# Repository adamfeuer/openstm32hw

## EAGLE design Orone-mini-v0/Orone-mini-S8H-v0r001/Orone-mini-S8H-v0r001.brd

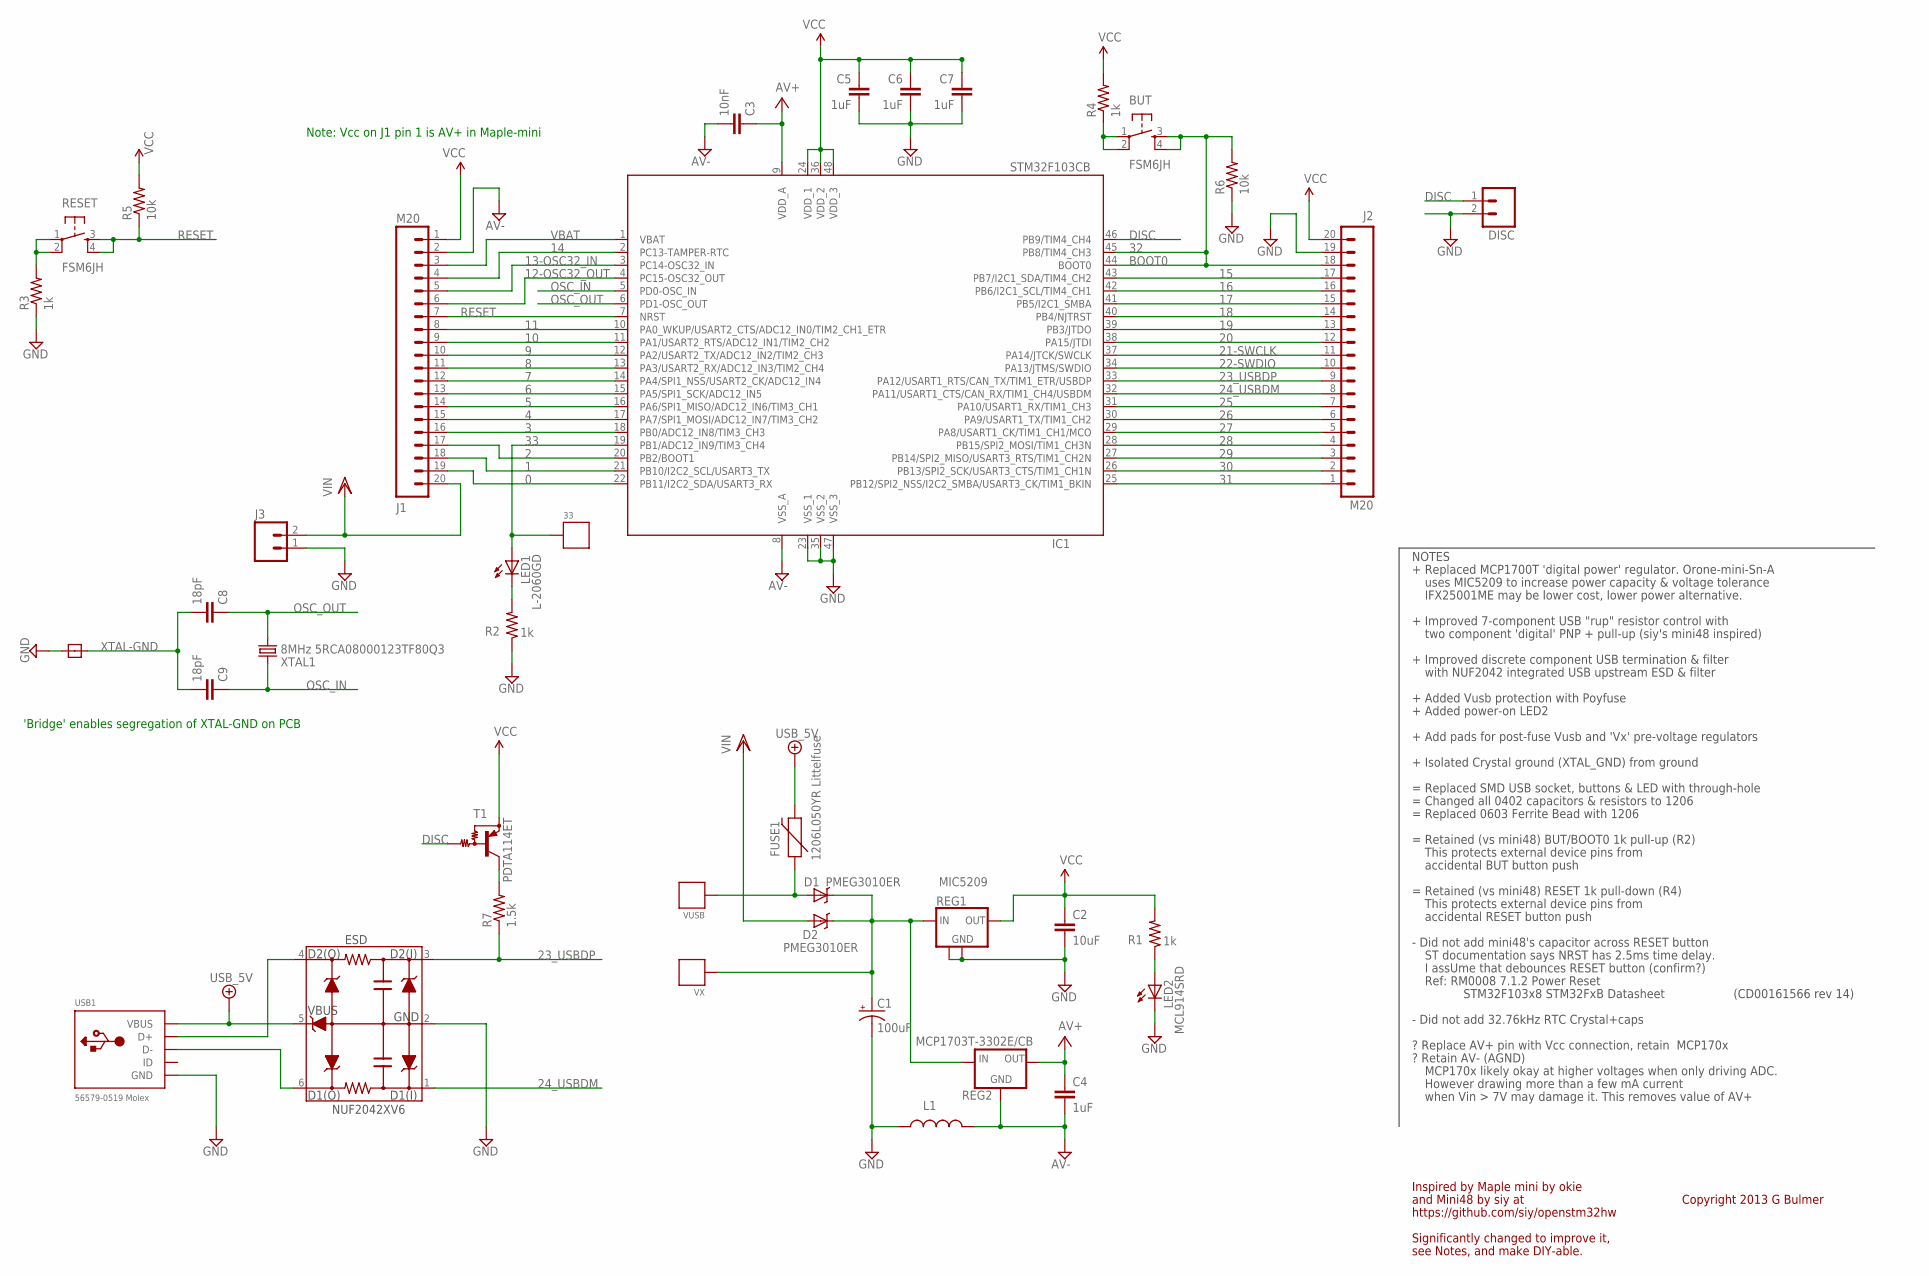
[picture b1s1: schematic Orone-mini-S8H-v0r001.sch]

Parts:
33: SIGNAL-PIN1; 1PIN
BUT: FSM6JH; TACTILE-PTH
C1: 100uF; EIA7343
C2: 10uF; 1206
C3: 10nF; 1206
C4, C5, C6, C7: 1uF; 1206
C8, C9: 18pF; 1206
D1, D2: PMEG3010ER; SOD-123W
DISC: M021X02_NO_SILK; 1X02_NO_SILK
ESD: NUF2042XV6; SOT563
FUSE1: 1206L050YR Littelfuse; PTC-1206
IC1: STM32F103CB; LQFP48
J1, J2: M20; 1X20
J3: M02POLAR; MOLEX-1X2
L1: INDUCTOR1206; 1206
LED1: L-2060GD; LED1.8MM-1MM
LED2: MCL914SRD; LED1.8MM-1MM
R1, R2, R3, R4: 1k; 1206
R5, R6: 10k; 1206
R7: 1.5k; 1206
REG1: MIC5209; SOT223-NT
REG2: MCP1703T-3302E/CB; SOT23
RESET: FSM6JH; TACTILE-PTH
T1: PDTA114ET; ES_SOT23-3
U$4: 2PIN-GND-BRIDGE08X08MILS; 2PIN-08X08
USB1: 56579-0519 Molex; USB-MINI-AB-TH-MOLEX-DRILL
VUSB: SIGNAL-PIN1; 1PIN
VX: SIGNAL-PIN1; 1PIN
XTAL1: 8MHz 5RCA08000123TF80Q3; CRYSTAL-SMD-5X3

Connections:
0: IC1.22 (PB11/I2C2_SDA/USART3_RX), J1.19
1: IC1.21 (PB10/I2C2_SCL/USART3_TX), J1.18
2: IC1.20 (PB2/BOOT1), J1.17
3: IC1.18 (PB0/ADC12_IN8/TIM3_CH3), J1.16
4: IC1.17 (PA7/SPI1_MOSI/ADC12_IN7/TIM3_CH2), J1.15
5: IC1.16 (PA6/SPI1_MISO/ADC12_IN6/TIM3_CH1), J1.14
6: IC1.15 (PA5/SPI1_SCK/ADC12_IN5), J1.13
7: IC1.14 (PA4/SPI1_NSS/USART2_CK/ADC12_IN4), J1.12
8: IC1.13 (PA3/USART2_RX/ADC12_IN3/TIM2_CH4), J1.11
9: IC1.12 (PA2/USART2_TX/ADC12_IN2/TIM2_CH3), J1.10
10: IC1.11 (PA1/USART2_RTS/ADC12_IN1/TIM2_CH2), J1.9
11: IC1.10 (PA0_WKUP/USART2_CTS/ADC12_IN0/TIM2_CH1_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), J1.8
12-OSC32_OUT: IC1.4 (PC15-OSC32_OUT), J1.6
13-OSC32_IN: IC1.3 (PC14-OSC32_IN), J1.5
14: IC1.2 (PC13-TAMPER-RTC), J1.4
15: IC1.43 (PB7/I2C1_SDA/TIM4_CH2), J2.17
16: IC1.42 (PB6/I2C1_SCL/TIM4_CH1), J2.16
17: IC1.41 (PB5/I2C1_SMBA), J2.15
18: IC1.40 (PB4/NJTRST), J2.14
19: IC1.39 (PB3/JTDO), J2.13
20: IC1.38 (PA15/JTDI), J2.12
21-SWCLK: IC1.37 (PA14/JTCK/SWCLK), J2.11
22-SWDIO: IC1.34 (PA13/JTMS/SWDIO), J2.10
23_USBDP: ESD.3 (D2(I)), IC1.33 (PA12/USART1_RTS/CAN_TX/TIM1_ETR/USBDP), J2.9, R7.1
24_USBDM: ESD.1 (D1(I)), IC1.32 (PA11/USART1_CTS/CAN_RX/TIM1_CH4/USBDM), J2.8
25: IC1.31 (PA10/USART1_RX/TIM1_CH3), J2.7
26: IC1.30 (PA9/USART1_TX/TIM1_CH2), J2.6
27: IC1.29 (PA8/USART1_CK/TIM1_CH1/MCO), J2.5
28: IC1.28 (PB15/SPI2_MOSI/TIM1_CH3N), J2.4
29: IC1.27 (PB14/SPI2_MISO/USART3_RTS/TIM1_CH2N), J2.3
30: IC1.26 (PB13/SPI2_SCK/USART3_CTS/TIM1_CH1N), J2.2
31: IC1.25 (PB12/SPI2_NSS/I2C2_SMBA/USART3_CK/TIM1_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), J2.1
32: BUT.3, BUT.4, IC1.44 (BOOT0), IC1.45 (PB8/TIM4_CH3), J2.18, R6.2
33: 33.P$1, IC1.19 (PB1/ADC12_IN9/TIM3_CH4), LED1.A
+5V/2: ESD.5 (VBUS), FUSE1.2, USB1.VBUS
AV+: C3.1, C4.1, IC1.9 (VDD_A), REG2.2 (OUT)
AV-: C3.2, C4.2, IC1.8 (VSS_A), J1.2, L1.2, REG2.1 (GND)
DGND: C1.C (-), C2.2, C5.2, C6.2, C7.2, DISC.2, ESD.2 (GND), IC1.23 (VSS_1), IC1.35 (VSS_2), IC1.47 (VSS_3), J2.19, J3.1, L1.1, LED2.C, R2.1, R3.1, R6.1, REG1.2 (GND), REG1.4 (GND), U$4.P$1, USB1.GND
DISC: DISC.1, IC1.46 (PB9/TIM4_CH4), T1.1 (B)
unnamed: BUT.1, BUT.2, R4.1
unnamed: LED1.C, R2.2
unnamed: D1.P$2.ANODE (A), FUSE1.1, VUSB.P$1
unnamed: R3.2, RESET.1, RESET.2
unnamed: LED2.A, R1.1
unnamed: C1.A (+), D1.P$1.CATHODE (C), D2.P$1.CATHODE (C), REG1.1 (IN), REG2.3 (IN), VX.P$1
unnamed: R7.2, T1.3 (C)
unnamed: ESD.4 (D2(O)), USB1.D+
unnamed: ESD.6 (D1(O)), USB1.D-
OSC_IN: C9.1, IC1.5 (PD0-OSC_IN), XTAL1.3 (2)
OSC_OUT: C8.1, IC1.6 (PD1-OSC_OUT), XTAL1.1
RESET: IC1.7 (NRST), J1.7, R5.1, RESET.3, RESET.4
VBAT: IC1.1 (VBAT), J1.3
VCC: C2.1, C5.1, C6.1, C7.1, IC1.24 (VDD_1), IC1.36 (VDD_2), IC1.48 (VDD_3), J1.1, J2.20, R1.2, R4.2, R5.2, REG1.3 (OUT), T1.2 (E)
VIN: D2.P$2.ANODE (A), J1.20, J3.2
XTAL-GND: C8.2, C9.2, U$4.P$2

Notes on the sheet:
BOOT0
NOTES
- Did not add 32.76kHz RTC Crystal+caps
? Retain AV- (AGND)
ST documentation says NRST has 2.5ms time delay.
Inspired by Maple mini by okie
and Mini48 by siy at
https://github.com/siy/openstm32hw
Copyright 2013 G Bulmer
I assUme that debounces RESET button (confirm?)
Ref: RM0008 7.1.2 Power Reset
STM32F103x8 STM32FxB Datasheet
(CD00161566 rev 14)
= Changed all 0402 capacitors & resistors to 1206
+ Replaced MCP1700T 'digital power' regulator. Orone-mini-Sn-A
uses MIC5209 to increase power capacity & voltage tolerance
+ Improved 7-component USB "rup" resistor control with
two component 'digital' PNP + pull-up (siy's mini48 inspired)
+ Improved discrete component USB termination & filter
with NUF2042 integrated USB upstream ESD & filter
= Replaced SMD USB socket, buttons & LED with through-hole
= Retained (vs mini48) RESET 1k pull-down (R4)
This protects external device pins from
accidental RESET button push
= Retained (vs mini48) BUT/BOOT0 1k pull-up (R2)
accidental BUT button push
- Did not add mini48's capacitor across RESET button
MCP170x likely okay at higher voltages when only driving ADC.
However drawing more than a few mA current
when Vin > 7V may damage it. This removes value of AV+
= Replaced 0603 Ferrite Bead with 1206
? Replace AV+ pin with Vcc connection, retain MCP170x
+ Added Vusb protection with Poyfuse
Note: Vcc on J1 pin 1 is AV+ in Maple-mini
'Bridge' enables segregation of XTAL-GND on PCB
+ Added power-on LED2
+ Isolated Crystal ground (XTAL_GND) from ground
Significantly changed to improve it,
see Notes, and make DIY-able.
IFX25001ME may be lower cost, lower power alternative.

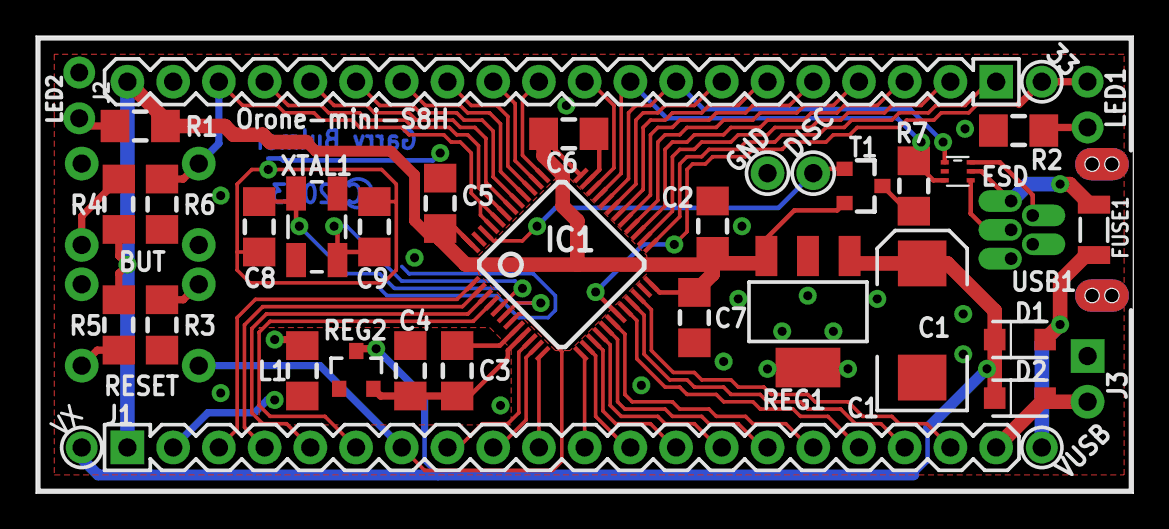
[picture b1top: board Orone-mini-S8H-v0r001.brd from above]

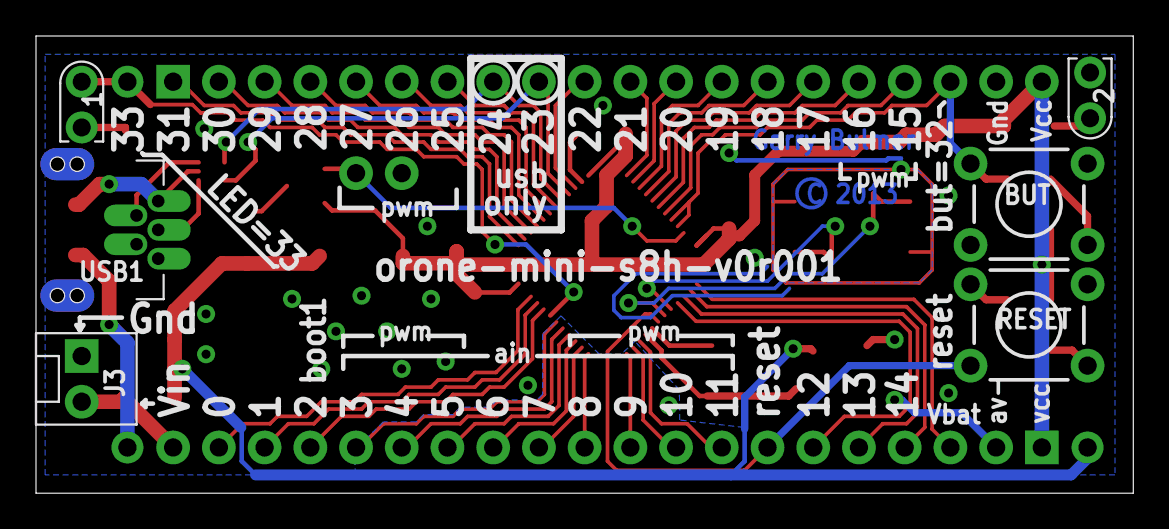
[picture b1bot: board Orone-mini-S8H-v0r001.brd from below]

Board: 2 copper layers, 61.0 x 25.4 mm, 39 parts (7 on the bottom side), 55 nets.

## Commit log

2013-06-27 adding new Digikey BOM files
2013-06-27 added 3 drill holes per side to the USB connector feet slots - to see if they will join into a continuous slot
2013-06-28 added 2 drill holes per connector foot to make the slots neater
2013-06-28 update board and schematic to use new usb conector package with added drill holes in overdrill style
2013-08-28 corrected error in Digikey2 BOM - replaced incorrect 1206 capacitor with correct EIA7343 version that is known to work
2013-08-28 added correct Digikey2 BOM - replaced incorrect 1206 capacitor with correct EIA7343 version that is known to work
